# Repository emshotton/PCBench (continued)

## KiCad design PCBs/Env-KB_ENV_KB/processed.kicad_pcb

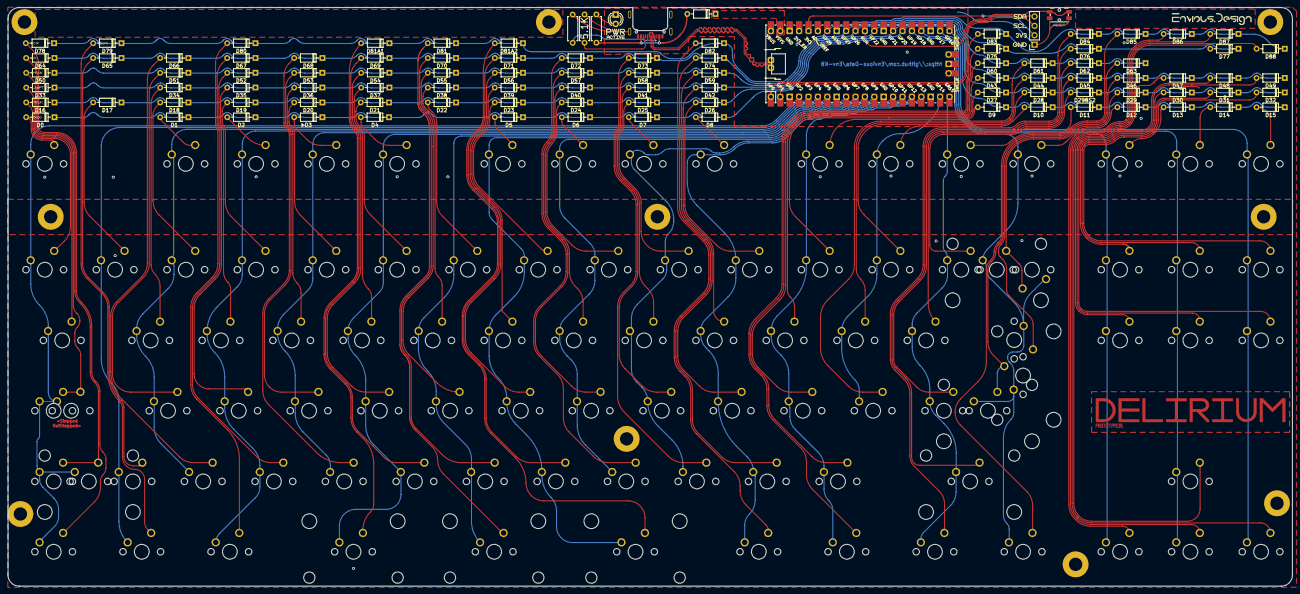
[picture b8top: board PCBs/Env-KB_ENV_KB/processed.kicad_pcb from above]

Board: 2 copper layers, 347.0 x 156.3 mm, 231 parts (0 on the bottom side), 128 nets.

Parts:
D0, D1, D2, D3, D4, D5, D6, D7, D8, D9, D10, D11, D12, D13, D14, D15, D16, D17, D18, D19, D20, D21, D22, D23, D24, D25, D26, D27, D28, D29, D29BS2, D30, D31, D32, D33, D34, D35, D36, D37, D38, D39, D40, D41, D42, D43, D44, D45, D46, D47, D48, D49, D50, D51, D52, D53, D54, D55, D56, D57, D58, D59, D60, D61, D62, D63, D64, D65, D66, D67, D68, D69, D70, D71, D72, D73, D74, D75, D76, D77, D78, D79, D80, D81, D81A1, D81A2, D82, D83, D84, D85, D86, D87, D88: D; D_DO-35_SOD27_P7.62mm_Horizontal
D89: 1n4002; D_DO-35_SOD27_P7.62mm_Horizontal
H0, H1, H3, H4, H4#2, H6, H7, H9, H10, H11: MountingHole; MountingHole_2.2mm_M2_Pad
I2CHeader0: Conn_01x04; PinSocket_1x04_P2.54mm_Vertical
K_0, K_1, K_2, K_3, K_4, K_5, K_6, K_7, K_8, K_9, K_10, K_11, K_12, K_13, K_14, K_15, K_16, K_17, K_18, K_19, K_20, K_21, K_22, K_23, K_24, K_25, K_26, K_27, K_28, K_29, K_29BS1, K_29BS2, K_30, K_31, K_32, K_34, K_35, K_36, K_37, K_38, K_39, K_40, K_41, K_42, K_43, K_44, K_45, K_47, K_48, K_49, K_51, K_52, K_53, K_54, K_55, K_56, K_57, K_58, K_59, K_60, K_61, K_62, K_65, K_66, K_67, K_68, K_69, K_70, K_71, K_72, K_73, K_74, K_75, K_77, K_81, K_81A1, K_81A2, K_86, K_87, K_88: KEYSW; MXOnly-1U-NoLED
K_33, K_46: KEYSW; MXOnly-1.5U-NoLED
K_50: KEYSW; MXOnly-1.75U-NoLED
K_50A1, K_64, K_78, K_79, K_80, K_82, K_83, K_84, K_85: KEYSW; MXOnly-1.25U-NoLED
K_63: MX-NoLED; MXOnly-1U-NoLED
K_63B1: MX-NoLED; MXOnly-2.25U-NoLED
K_64B1: KEYSW; MXOnly-2.25U-NoLED
K_76: KEYSW; MXOnly-2.75U-NoLED
PowerLED0: LED 3mm; LED_D3.0mm
PowerLedResistor0: 47K Resistor; R_Axial_DIN0207_L6.3mm_D2.5mm_P7.62mm_Horizontal
RESISTOR0, RESISTOR1: 5.1k; R_Axial_DIN0207_L6.3mm_D2.5mm_P7.62mm_Horizontal
RPI0: Pico; RPi_Pico_SMD_TH
STAB1, STAB2, STAB3, STAB4, STAB5: Stabilizer; Stabilizer_Cherry_MX_2u
SW-RST0: EVQ; Panasonic_EVQPUL_EVQPUC
USB1: HRO-TYPE-C-31-M-12; USB_C_TYPE-C-31-M-14
kibuzzard-628ADF99, kibuzzard-628ADF99#2: G***; kibuzzard-628ADF99
kibuzzard-628AE7EF: G***; kibuzzard-628AE7EF
kibuzzard-628AE7FB: G***; kibuzzard-628AE7FB
kibuzzard-628AE8A6: G***; kibuzzard-628AE8A6
kibuzzard-628AE061, kibuzzard-628AE061#2: G***; kibuzzard-628AE061
kibuzzard-628AE80F: G***; kibuzzard-628AE80F
kibuzzard-628AE82F: G***; kibuzzard-628AE82F
kibuzzard-628AE768: G***; kibuzzard-628AE768
kibuzzard-628AE805: G***; kibuzzard-628AE805
kibuzzard-628AE860: G***; kibuzzard-628AE860
kibuzzard-628AE868: G***; kibuzzard-628AE868
kibuzzard-628AE874: G***; kibuzzard-628AE874
kibuzzard-628AE882: G***; kibuzzard-628AE882
kibuzzard-628AE933: G***; kibuzzard-628AE933
kibuzzard-628AE966: G***; kibuzzard-628AE966
kibuzzard-628AEA91: G***; kibuzzard-628AEA91
kibuzzard-6250C4E7: G***; kibuzzard-6250C4E7

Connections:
3.3V: I2CHeader0.2, RPI0.36 (3V3)
GND: I2CHeader0.1, PowerLED0.1 (K), RESISTOR0.2, RESISTOR1.1, RPI0.3 (GND), RPI0.8 (GND), RPI0.13 (GND), RPI0.18 (GND), RPI0.23 (GND), RPI0.28 (GND), RPI0.38 (GND), SW-RST0.2, USB1.A1 (GND), USB1.A12 (GND), USB1.B1 (GND), USB1.B12 (GND), USB1.S1 (SHIELD)
I2CSCL: I2CHeader0.3, RPI0.2 (GPIO1)
I2CSDA: I2CHeader0.4, RPI0.1 (GPIO0)
unnamed: D0.2 (A), K_0.2 (ROW)
unnamed: D1.2 (A), K_1.2 (ROW)
unnamed: D2.2 (A), K_2.2 (ROW)
unnamed: D3.2 (A), K_3.2 (ROW)
unnamed: D4.2 (A), K_4.2 (ROW)
unnamed: D5.2 (A), K_5.2 (ROW)
unnamed: D6.2 (A), K_6.2 (ROW)
unnamed: D7.2 (A), K_7.2 (ROW)
unnamed: D8.2 (A), K_8.2 (ROW)
unnamed: D9.2 (A), K_9.2 (ROW)
unnamed: D10.2 (A), K_10.2 (ROW)
unnamed: D11.2 (A), K_11.2 (ROW)
unnamed: D12.2 (A), K_12.2 (ROW)
unnamed: D13.2 (A), K_13.2 (ROW)
unnamed: D14.2 (A), K_14.2 (ROW)
unnamed: D15.2 (A), K_15.2 (ROW)
unnamed: D16.2 (A), K_16.2 (ROW)
unnamed: D17.2 (A), K_17.2 (ROW)
unnamed: D18.2 (A), K_18.2 (ROW)
unnamed: D19.2 (A), K_19.2 (ROW)
unnamed: D20.2 (A), K_20.2 (ROW)
unnamed: D21.2 (A), K_21.2 (ROW)
unnamed: D22.2 (A), K_22.2 (ROW)
unnamed: D23.2 (A), K_23.2 (ROW)
unnamed: D24.2 (A), K_24.2 (ROW)
unnamed: D25.2 (A), K_25.2 (ROW)
unnamed: D26.2 (A), K_26.2 (ROW)
unnamed: D27.2 (A), K_27.2 (ROW)
unnamed: D28.2 (A), K_28.2 (ROW)
unnamed: D29.2 (A), K_29.2 (ROW), K_29BS1.2 (ROW)
unnamed: D29BS2.2 (A), K_29BS2.2 (ROW)
unnamed: D30.2 (A), K_30.2 (ROW)
unnamed: D31.2 (A), K_31.2 (ROW)
unnamed: D32.2 (A), K_32.2 (ROW)
unnamed: D33.2 (A), K_33.2 (ROW)
unnamed: D34.2 (A), K_34.2 (ROW)
unnamed: D35.2 (A), K_35.2 (ROW)
unnamed: D36.2 (A), K_36.2 (ROW)
unnamed: D37.2 (A), K_37.2 (ROW)
unnamed: D38.2 (A), K_38.2 (ROW)
unnamed: D39.2 (A), K_39.2 (ROW)
unnamed: D40.2 (A), K_40.2 (ROW)
unnamed: D41.2 (A), K_41.2 (ROW)
unnamed: D42.2 (A), K_42.2 (ROW)
unnamed: D43.2 (A), K_43.2 (ROW)
unnamed: D44.2 (A), K_44.2 (ROW)
unnamed: D45.2 (A), K_45.2 (ROW)
unnamed: D46.2 (A), K_46.2 (ROW)
unnamed: D47.2 (A), K_47.2 (ROW)
unnamed: D48.2 (A), K_48.2 (ROW)
unnamed: D49.2 (A), K_49.2 (ROW)
unnamed: D50.2 (A), K_50.2 (ROW), K_50A1.2 (ROW)
unnamed: D51.2 (A), K_51.2 (ROW)
unnamed: D52.2 (A), K_52.2 (ROW)
unnamed: D53.2 (A), K_53.2 (ROW)
unnamed: D54.2 (A), K_54.2 (ROW)
unnamed: D55.2 (A), K_55.2 (ROW)
unnamed: D56.2 (A), K_56.2 (ROW)
unnamed: D57.2 (A), K_57.2 (ROW)
unnamed: D58.2 (A), K_58.2 (ROW)
unnamed: D59.2 (A), K_59.2 (ROW)
unnamed: D60.2 (A), K_60.2 (ROW)
unnamed: D61.2 (A), K_61.2 (ROW)
unnamed: D62.2 (A), K_62.2 (ROW)
unnamed: D63.2 (A), K_63.2, K_63B1.2 (ROW)
unnamed: D64.2 (A), K_64.2 (ROW), K_64B1.2 (ROW)
unnamed: D65.2 (A), K_65.2 (ROW)
unnamed: D66.2 (A), K_66.2 (ROW)
unnamed: D67.2 (A), K_67.2 (ROW)
unnamed: D68.2 (A), K_68.2 (ROW)
unnamed: D69.2 (A), K_69.2 (ROW)
unnamed: D70.2 (A), K_70.2 (ROW)
unnamed: D71.2 (A), K_71.2 (ROW)
unnamed: D72.2 (A), K_72.2 (ROW)
unnamed: D73.2 (A), K_73.2 (ROW)
unnamed: D74.2 (A), K_74.2 (ROW)
unnamed: D75.2 (A), K_75.2 (ROW)
unnamed: D76.2 (A), K_76.2 (ROW)
unnamed: D77.2 (A), K_77.2 (ROW)
unnamed: D78.2 (A), K_78.2 (ROW)
unnamed: D79.2 (A), K_79.2 (ROW)
unnamed: D80.2 (A), K_80.2 (ROW)
unnamed: D81.2 (A), K_81.2 (ROW)
unnamed: D81A1.2 (A), K_81A1.2 (ROW)
unnamed: D81A2.2 (A), K_81A2.2 (ROW)
unnamed: D82.2 (A), K_82.2 (ROW)
unnamed: D83.2 (A), K_83.2 (ROW)
unnamed: D84.2 (A), K_84.2 (ROW)
unnamed: D85.2 (A), K_85.2 (ROW)
unnamed: D86.2 (A), K_86.2 (ROW)
unnamed: D87.2 (A), K_87.2 (ROW)
unnamed: D88.2 (A), K_88.2 (ROW)
unnamed: PowerLED0.2 (A), PowerLedResistor0.2
unnamed: RESISTOR0.1, USB1.B5 (CC2)
unnamed: RESISTOR1.2, USB1.A5 (CC1)
Resetbtn: RPI0.30 (RUN), SW-RST0.1
USB2_N: RPI0.TP2 (USB_DM), USB1.A7 (D-), USB1.B7 (D-)
USB2_P: RPI0.TP3 (USB_DP), USB1.A6 (D+), USB1.B6 (D+)
USBVBUS: D89.2 (A), PowerLedResistor0.1, USB1.A4 (VBUS), USB1.A9 (VBUS), USB1.B4 (VBUS), USB1.B9 (VBUS)
VSYS: D89.1 (K), RPI0.39 (VSYS)
col0: K_0.1 (COL), K_16.1 (COL), K_33.1 (COL), K_50.1 (COL), K_50A1.1 (COL), K_64.1 (COL), K_64B1.1 (COL), K_78.1 (COL), RPI0.4 (GPIO2)
col1: K_17.1 (COL), K_65.1 (COL), K_79.1 (COL), RPI0.5 (GPIO3)
col2: K_1.1 (COL), K_18.1 (COL), K_34.1 (COL), K_51.1 (COL), K_66.1 (COL), RPI0.6 (GPIO4)
col3: K_2.1 (COL), K_19.1 (COL), K_35.1 (COL), K_52.1 (COL), K_67.1 (COL), K_80.1 (COL), RPI0.7 (GPIO5)
col4: K_3.1 (COL), K_20.1 (COL), K_36.1 (COL), K_53.1 (COL), K_68.1 (COL), RPI0.9 (GPIO6)
col5: K_4.1 (COL), K_21.1 (COL), K_37.1 (COL), K_54.1 (COL), K_69.1 (COL), K_81A1.1 (COL), RPI0.10 (GPIO7)
col6: K_22.1 (COL), K_38.1 (COL), K_55.1 (COL), K_70.1 (COL), K_81.1 (COL), RPI0.11 (GPIO8)
col7: K_5.1 (COL), K_23.1 (COL), K_39.1 (COL), K_56.1 (COL), K_71.1 (COL), K_81A2.1 (COL), RPI0.12 (GPIO9)
col8: K_6.1 (COL), K_24.1 (COL), K_40.1 (COL), K_57.1 (COL), K_72.1 (COL), RPI0.14 (GPIO10)
col9: K_7.1 (COL), K_25.1 (COL), K_41.1 (COL), K_58.1 (COL), K_73.1 (COL), RPI0.15 (GPIO11)
col10: K_8.1 (COL), K_26.1 (COL), K_42.1 (COL), K_59.1 (COL), K_74.1 (COL), K_82.1 (COL), RPI0.16 (GPIO12)
col11: K_9.1 (COL), K_27.1 (COL), K_43.1 (COL), K_60.1 (COL), K_75.1 (COL), K_83.1 (COL), RPI0.17 (GPIO13)
col12: K_10.1 (COL), K_28.1 (COL), K_44.1 (COL), K_61.1 (COL), RPI0.19 (GPIO14)
col13: K_11.1 (COL), K_29BS2.1 (COL), K_45.1 (COL), K_62.1 (COL), K_76.1 (COL), K_84.1 (COL), RPI0.20 (GPIO15)
col14: K_12.1 (COL), K_29.1 (COL), K_29BS1.1 (COL), K_46.1 (COL), K_63.1, K_63B1.1 (COL), K_85.1 (COL), RPI0.25 (GPIO19)
col15: K_13.1 (COL), K_30.1 (COL), K_47.1 (COL), K_86.1 (COL), RPI0.24 (GPIO18)
col16: K_14.1 (COL), K_31.1 (COL), K_48.1 (COL), K_77.1 (COL), K_87.1 (COL), RPI0.22 (GPIO17)
col17: K_15.1 (COL), K_32.1 (COL), K_49.1 (COL), K_88.1 (COL), RPI0.21 (GPIO16)
row0: D0.1 (K), D1.1 (K), D2.1 (K), D3.1 (K), D4.1 (K), D5.1 (K), D6.1 (K), D7.1 (K), D8.1 (K), D9.1 (K), D10.1 (K), D11.1 (K), D12.1 (K), D13.1 (K), D14.1 (K), D15.1 (K), RPI0.26 (GPIO20)
row2: D16.1 (K), D17.1 (K), D18.1 (K), D19.1 (K), D20.1 (K), D21.1 (K), D22.1 (K), D23.1 (K), D24.1 (K), D25.1 (K), D26.1 (K), D27.1 (K), D28.1 (K), D29.1 (K), D29BS2.1 (K), D30.1 (K), D31.1 (K), D32.1 (K), RPI0.27 (GPIO21)
row3: D33.1 (K), D34.1 (K), D35.1 (K), D36.1 (K), D37.1 (K), D38.1 (K), D39.1 (K), D40.1 (K), D41.1 (K), D42.1 (K), D43.1 (K), D44.1 (K), D45.1 (K), D46.1 (K), D47.1 (K), D48.1 (K), D49.1 (K), RPI0.29 (GPIO22)
row4: D50.1 (K), D51.1 (K), D52.1 (K), D53.1 (K), D54.1 (K), D55.1 (K), D56.1 (K), D57.1 (K), D58.1 (K), D59.1 (K), D60.1 (K), D61.1 (K), D62.1 (K), D63.1 (K), RPI0.31 (GPIO26_ADC0)
row5: D64.1 (K), D65.1 (K), D66.1 (K), D67.1 (K), D68.1 (K), D69.1 (K), D70.1 (K), D71.1 (K), D72.1 (K), D73.1 (K), D74.1 (K), D75.1 (K), D76.1 (K), D77.1 (K), RPI0.32 (GPIO27_ADC1)
row6: D78.1 (K), D79.1 (K), D80.1 (K), D81.1 (K), D81A1.1 (K), D81A2.1 (K), D82.1 (K), D83.1 (K), D84.1 (K), D85.1 (K), D86.1 (K), D87.1 (K), D88.1 (K), RPI0.34 (GPIO28_ADC2)
